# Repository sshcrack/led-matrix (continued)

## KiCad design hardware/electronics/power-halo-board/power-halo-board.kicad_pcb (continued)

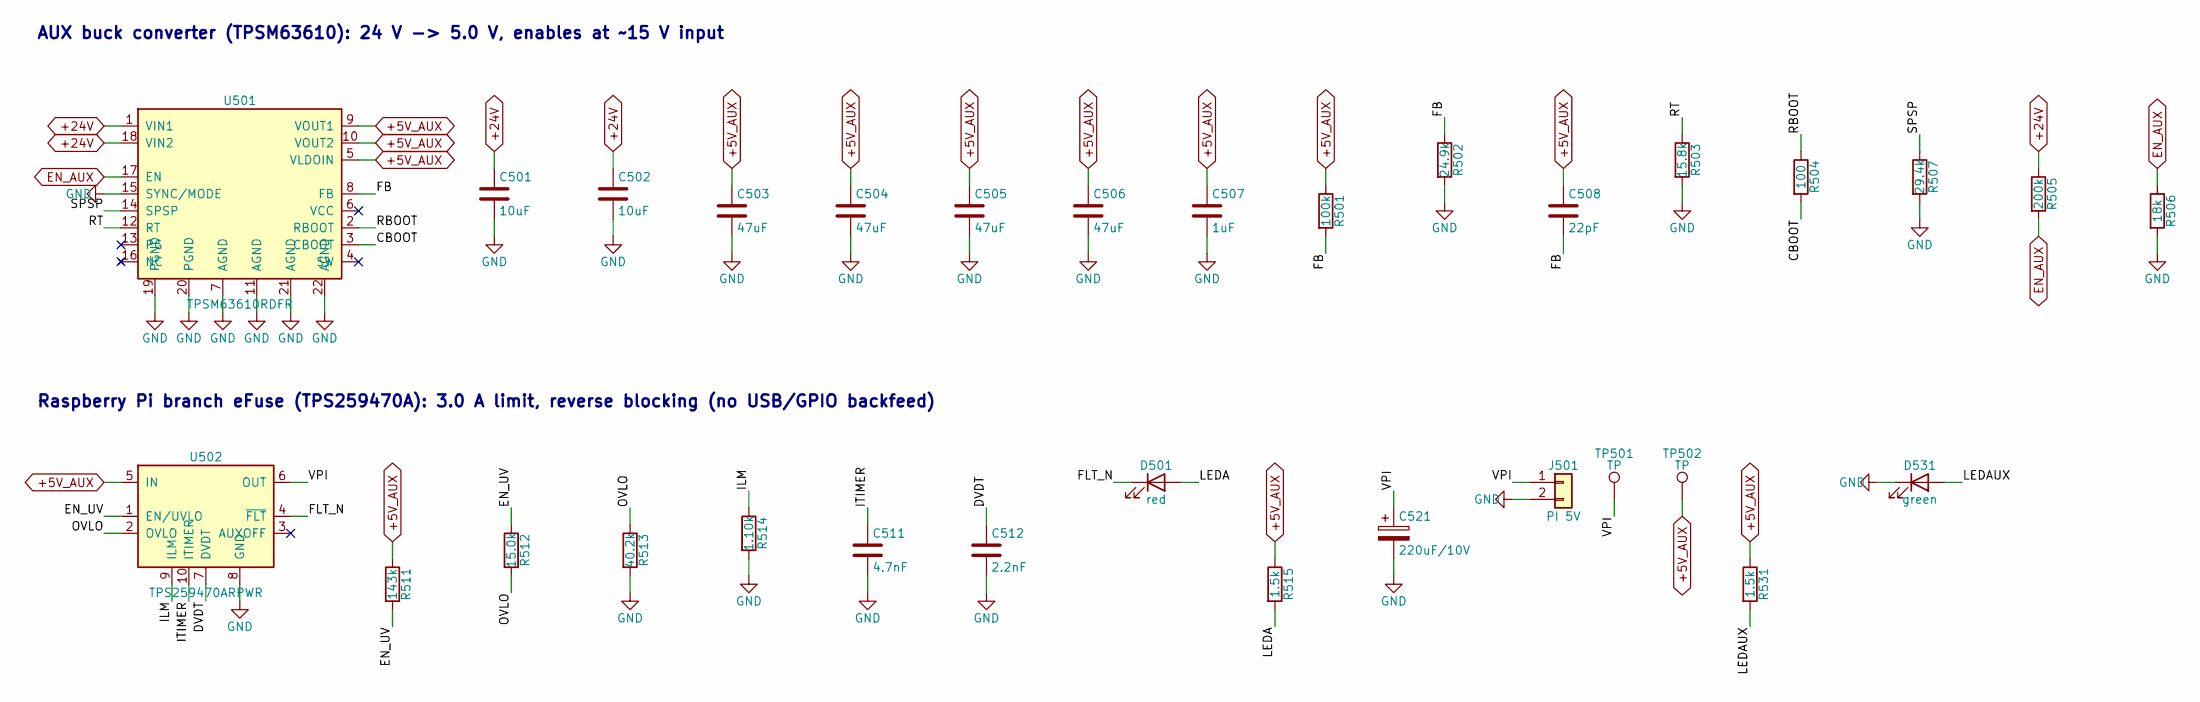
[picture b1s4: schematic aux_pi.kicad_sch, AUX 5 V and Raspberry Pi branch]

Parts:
C501, C502: 10uF; C_1210_3225Metric; Rating 50 V X7R; MPN GRM32ER71H106KA12L
C503, C504, C505, C506: 47uF; C_1210_3225Metric; Rating 10 V X7R; MPN GRM32ER71A476ME15L
C507: 1uF; C_0603_1608Metric; Rating 16 V X7R; MPN GRM188R71C105KA12D
C508: 22pF; C_0603_1608Metric; Rating 50 V C0G; MPN GRM1885C1H220JA01D
C511: 4.7nF; C_0603_1608Metric; Rating 50 V X7R; MPN GRM188R71H472KA01D
C512: 2.2nF; C_0603_1608Metric; Rating 50 V X7R; MPN GRM188R71H222KA01D
C521: 220uF/10V; CP_Elec_8x6.2; Rating 10V; MPN EEE-FK1A221P
D501: red; LED_0603_1608Metric; Rating 20 mA max, run at ~2 mA; MPN APT1608EC
D531: green; LED_0603_1608Metric; Rating 20 mA max, run at ~2 mA; MPN APT1608SGC
J501: PI 5V; JST_VH_S2P-VH_1x02_P3.96mm_Horizontal; Rating 10 A/contact; MPN S2P-VH
R501: 100k; R_0603_1608Metric; Tolerance 1%; Rating 0.1 W, 75 V; MPN RC0603FR-07100KL
R502: 24.9k; R_0603_1608Metric; Tolerance 1%; Rating 0.1 W, 75 V; MPN RC0603FR-0724K9L
R503: 15.8k; R_0603_1608Metric; Tolerance 1%; Rating 0.1 W, 75 V; MPN RC0603FR-0715K8L
R504: 100; R_0603_1608Metric; Tolerance 1%; Rating 0.1 W, 75 V; MPN RC0603FR-07100RL
R505: 200k; R_0603_1608Metric; Tolerance 1%; Rating 0.1 W, 75 V; MPN RC0603FR-07200KL
R506: 18k; R_0603_1608Metric; Tolerance 1%; Rating 0.1 W, 75 V; MPN RC0603FR-0718KL
R507: 29.4k; R_0603_1608Metric; Tolerance 1%; Rating 0.1 W, 75 V; MPN RC0603FR-0729K4L
R511: 143k; R_0603_1608Metric; Tolerance 1%; Rating 0.1 W, 75 V; MPN RC0603FR-07143KL
R512: 15.0k; R_0603_1608Metric; Tolerance 1%; Rating 0.1 W, 75 V; MPN RC0603FR-0715K0L
R513: 40.2k; R_0603_1608Metric; Tolerance 1%; Rating 0.1 W, 75 V; MPN RC0603FR-0740K2L
R514: 1.10k; R_0603_1608Metric; Tolerance 1%; Rating 0.1 W, 75 V; MPN RC0603FR-071K10L
R515, R531: 1.5k; R_0603_1608Metric; Tolerance 1%; Rating 0.1 W, 75 V; MPN RC0603FR-071K5L
TP501, TP502: TP; TestPoint_Pad_D1.5mm
U501: TPSM63610RDFR; TI_RDF0022A_B3QFN-22_6.5x7.5mm; Rating VIN 3-36 V (42 V transient), 8 A; used 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; MPN TPSM63610RDFR
U502: TPS259470ARPWR; TI_RPW0010A_VQFN-HR-10_2x2mm; Rating 2.7-23 V (28 V abs), 5.5 A, 28 mOhm; MPN TPS259470ARPWR

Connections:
+5V_AUX: C503.1, C504.1, C505.1, C506.1, C507.1, C508.1, R501.1, R511.1, R515.1, R531.1, TP502.1, U501.5 (VLDOIN), U501.9 (VOUT1), U501.10 (VOUT2), U502.5 (IN); also elsewhere on the board
+24V: C501.1, C502.1, R505.1, U501.1 (VIN1), U501.18 (VIN2); also elsewhere on the board
/Aux/CBOOT: R504.2, U501.3 (CBOOT)
/Aux/DVDT: C512.1, U502.7 (DVDT)
/Aux/EN_UV: R511.2, R512.1, U502.1 (EN/UVLO)
/Aux/FB: C508.2, R501.2, R502.1, U501.8 (FB)
/Aux/FLT_N: D501.1 (K), U502.4 (~FLT)
/Aux/ILM: R514.1, U502.9 (ILM)
/Aux/ITIMER: C511.1, U502.10 (ITIMER)
/Aux/LEDA: D501.2 (A), R515.2
/Aux/LEDAUX: D531.2 (A), R531.2
/Aux/OVLO: R512.2, R513.1, U502.2 (OVLO)
/Aux/RBOOT: R504.1, U501.2 (RBOOT)
/Aux/RT: R503.1, U501.12 (RT)
/Aux/SPSP: R507.1, U501.14 (SPSP)
/Aux/VPI: C521.1, J501.1, TP501.1, U502.6 (OUT)
EN_AUX: R505.2, R506.1, U501.17 (EN); also elsewhere on the board
GND: C501.2, C502.2, C503.2, C504.2, C505.2, C506.2, C507.2, C511.2, C512.2, C521.2, D531.1 (K), J501.2, R502.2, R503.2, R506.2, R507.2, R513.2, R514.2, U501.7 (AGND), U501.11 (AGND), U501.15 (SYNC/MODE), U501.19 (PGND), U501.20 (PGND), U501.21 (AGND), U501.22 (AGND), U502.8 (GND); also elsewhere on the board

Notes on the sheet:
AUX buck converter (TPSM63610): 24 V -> 5.0 V, enables at ~15 V input
Raspberry Pi branch eFuse (TPS259470A): 3.0 A limit, reverse blocking (no USB/GPIO backfeed)

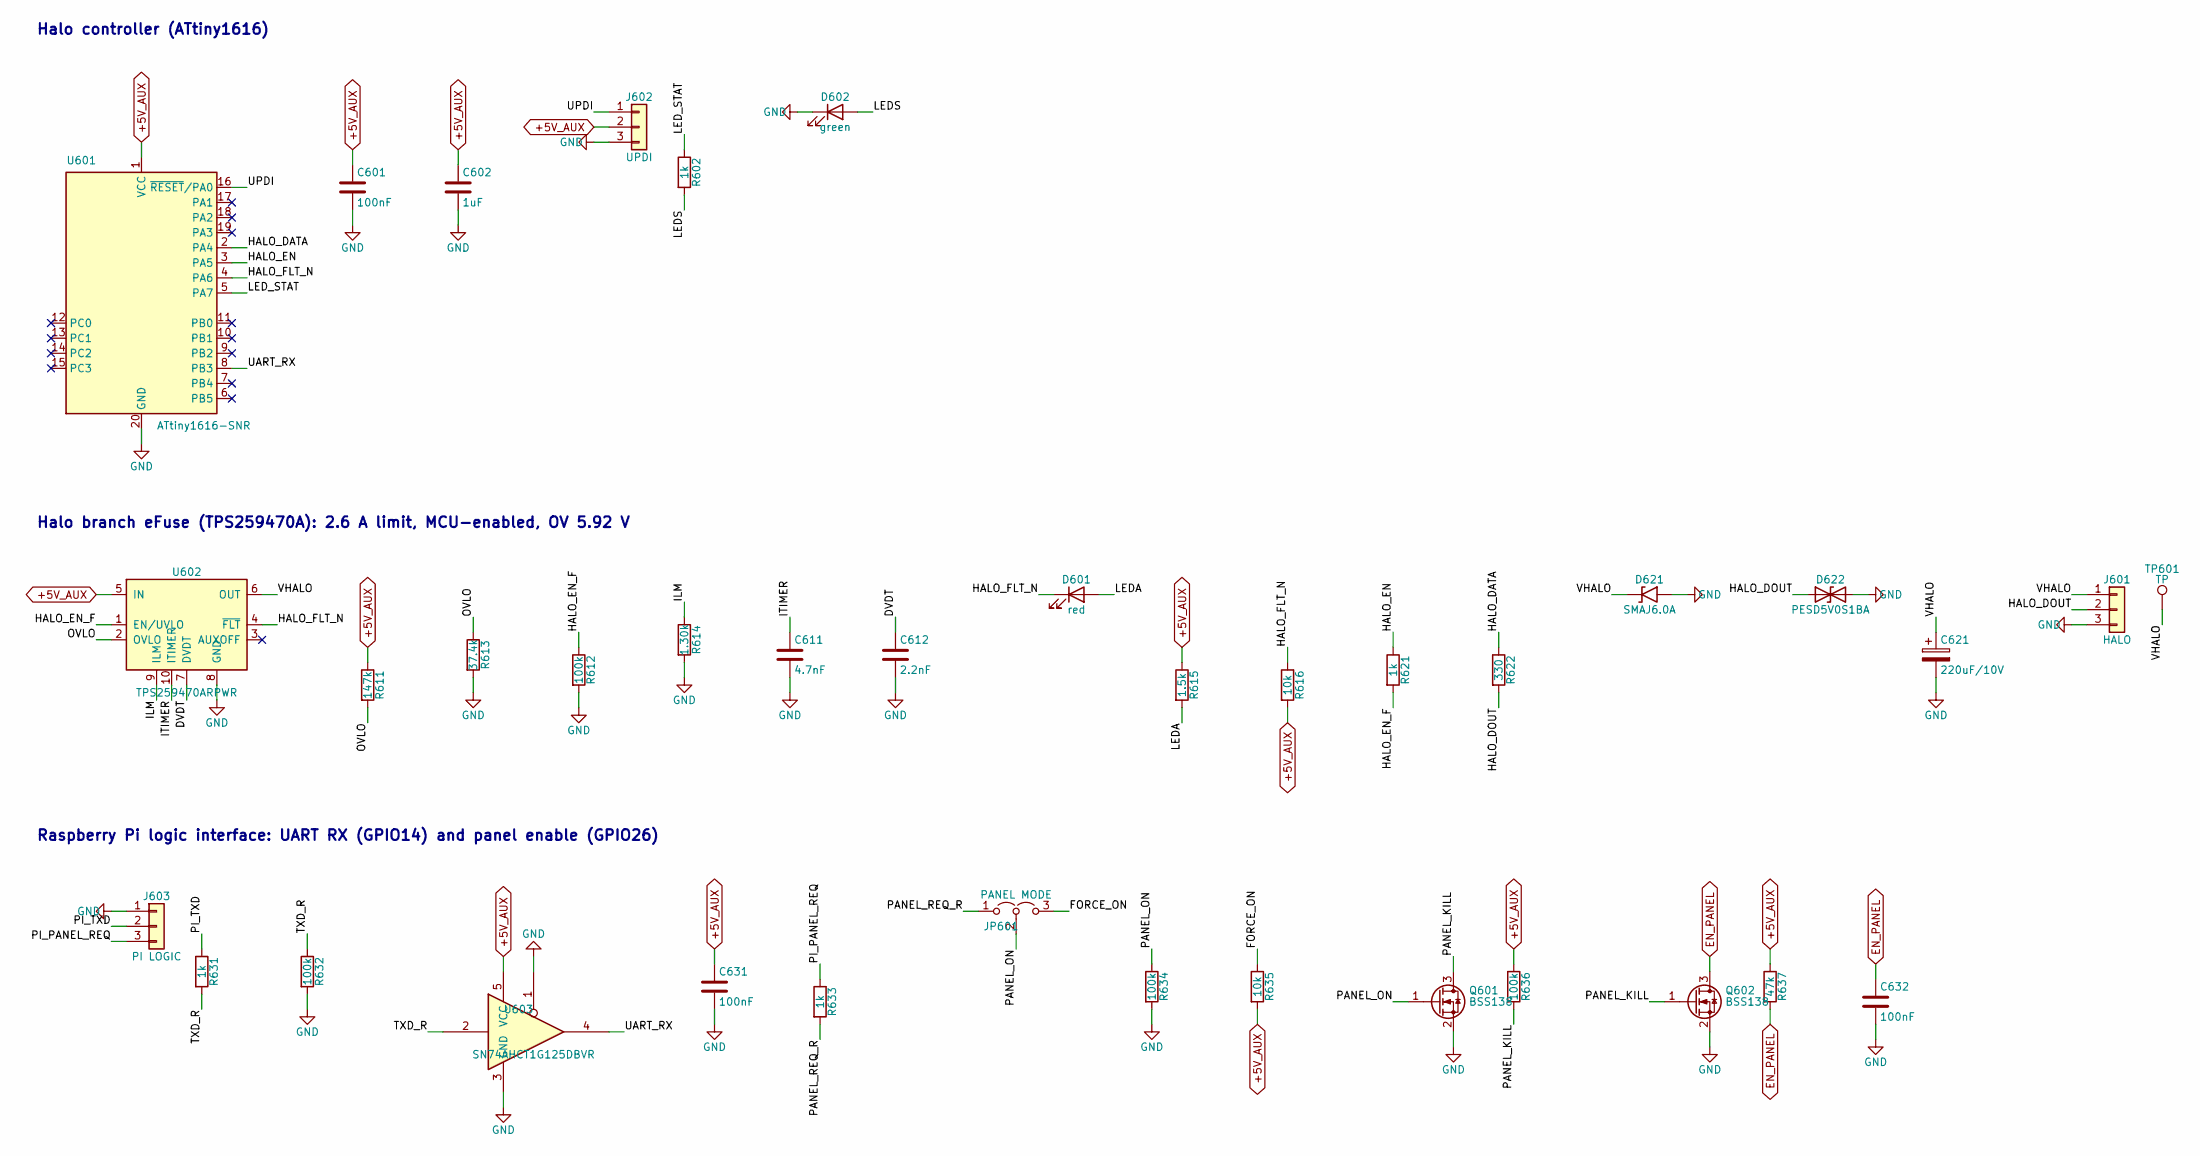
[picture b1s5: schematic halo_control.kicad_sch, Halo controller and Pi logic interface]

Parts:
C601, C631, C632: 100nF; C_0603_1608Metric; Rating 50 V X7R; MPN GRM188R71H104KA93D
C602: 1uF; C_0603_1608Metric; Rating 16 V X7R; MPN GRM188R71C105KA12D
C611: 4.7nF; C_0603_1608Metric; Rating 50 V X7R; MPN GRM188R71H472KA01D
C612: 2.2nF; C_0603_1608Metric; Rating 50 V X7R; MPN GRM188R71H222KA01D
C621: 220uF/10V; CP_Elec_8x6.2; Rating 10V; MPN EEE-FK1A221P
D601: red; LED_0603_1608Metric; Rating 20 mA max, run at ~2 mA; MPN APT1608EC
D602: green; LED_0603_1608Metric; Rating 20 mA max, run at ~2 mA; MPN APT1608SGC
D621: SMAJ6.0A; D_SMA; Rating VRWM 6.0 V, 400 W; MPN SMAJ6.0A
D622: PESD5V0S1BA; D_SOD-323; Rating VRWM 5 V; MPN PESD5V0S1BA
J601: HALO; JST_VH_S3P-VH_1x03_P3.96mm_Horizontal; Rating 10 A/contact; MPN S3P-VH
J602: UPDI; PinHeader_1x03_P2.54mm_Vertical; MPN 61300311121
J603: PI LOGIC; JST_XH_S3B-XH-A_1x03_P2.50mm_Horizontal; Rating 3 A/contact; MPN S3B-XH-A
JP601: PANEL MODE; PinHeader_1x03_P2.54mm_Vertical; MPN 61300311121
Q601: BSS138; SOT-23; Rating 50 V, 0.22 A, Vgs(th) <= 1.5 V; MPN BSS138
Q602: BSS138; SOT-23; Rating 50 V, 0.22 A; MPN BSS138
R602, R621, R631, R633: 1k; R_0603_1608Metric; Tolerance 1%; Rating 0.1 W, 75 V; MPN RC0603FR-071KL
R611: 147k; R_0603_1608Metric; Tolerance 1%; Rating 0.1 W, 75 V; MPN RC0603FR-07147KL
R612, R632, R634, R636: 100k; R_0603_1608Metric; Tolerance 1%; Rating 0.1 W, 75 V; MPN RC0603FR-07100KL
R613: 37.4k; R_0603_1608Metric; Tolerance 1%; Rating 0.1 W, 75 V; MPN RC0603FR-0737K4L
R614: 1.30k; R_0603_1608Metric; Tolerance 1%; Rating 0.1 W, 75 V; MPN RC0603FR-071K30L
R615: 1.5k; R_0603_1608Metric; Tolerance 1%; Rating 0.1 W, 75 V; MPN RC0603FR-071K5L
R616, R635: 10k; R_0603_1608Metric; Tolerance 1%; Rating 0.1 W, 75 V; MPN RC0603FR-0710KL
R622: 330; R_0603_1608Metric; Tolerance 1%; Rating 0.1 W, 75 V; MPN RC0603FR-07330RL
R637: 47k; R_0603_1608Metric; Tolerance 1%; Rating 0.1 W, 75 V; MPN RC0603FR-0747KL
TP601: TP; TestPoint_Pad_D1.5mm
U601: ATtiny1616-SNR; SOIC-20W_7.5x12.8mm_P1.27mm; Rating 1.8-5.5 V, 20 MHz at 4.5-5.5 V; MPN ATtiny1616-SNR
U602: TPS259470ARPWR; TI_RPW0010A_VQFN-HR-10_2x2mm; Rating 2.7-23 V (28 V abs), 5.5 A, 28 mOhm; MPN TPS259470ARPWR
U603: SN74AHCT1G125DBVR; SOT-23-5; Rating 4.5-5.5 V; MPN SN74AHCT1G125DBVR

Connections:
+5V_AUX: C601.1, C602.1, C631.1, J602.2, R611.1, R615.1, R616.2, R635.2, R636.1, R637.1, U601.1 (VCC), U602.5 (IN), U603.5 (VCC); also elsewhere on the board
/Halo/DVDT: C612.1, U602.7 (DVDT)
/Halo/FORCE_ON: JP601.3 (B), R635.1
/Halo/HALO_DATA: R622.1, U601.2 (PA4)
/Halo/HALO_DOUT: D622.1 (A1), J601.2, R622.2
/Halo/HALO_EN: R621.1, U601.3 (PA5)
/Halo/HALO_EN_F: R612.1, R621.2, U602.1 (EN/UVLO)
/Halo/HALO_FLT_N: D601.1 (K), R616.1, U601.4 (PA6), U602.4 (~FLT)
/Halo/ILM: R614.1, U602.9 (ILM)
/Halo/ITIMER: C611.1, U602.10 (ITIMER)
/Halo/LEDA: D601.2 (A), R615.2
/Halo/LEDS: D602.2 (A), R602.2
/Halo/LED_STAT: R602.1, U601.5 (PA7)
/Halo/OVLO: R611.2, R613.1, U602.2 (OVLO)
/Halo/PANEL_KILL: Q601.3 (D), Q602.1 (G), R636.2
/Halo/PANEL_ON: JP601.2 (C), Q601.1 (G), R634.1
/Halo/PANEL_REQ_R: JP601.1 (A), R633.2
/Halo/PI_PANEL_REQ: J603.3, R633.1
/Halo/PI_TXD: J603.2, R631.1
/Halo/TXD_R: R631.2, R632.1, U603.2
/Halo/UART_RX: U601.8 (PB3), U603.4
/Halo/UPDI: J602.1, U601.16 (~RESET/PA0)
/Halo/VHALO: C621.1, D621.1 (K), J601.1, TP601.1, U602.6 (OUT)
EN_PANEL: C632.1, Q602.3 (D), R637.2; also elsewhere on the board
GND: C601.2, C602.2, C611.2, C612.2, C621.2, C631.2, C632.2, D602.1 (K), D621.2 (A), D622.2 (A2), J601.3, J602.3, J603.1, Q601.2 (S), Q602.2 (S), R612.2, R613.2, R614.2, R632.2, R634.2, U601.20 (GND), U602.8 (GND), U603.1, U603.3 (GND); also elsewhere on the board

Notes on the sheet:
Halo controller (ATtiny1616)
Halo branch eFuse (TPS259470A): 2.6 A limit, MCU-enabled, OV 5.92 V
Raspberry Pi logic interface: UART RX (GPIO14) and panel enable (GPIO26)

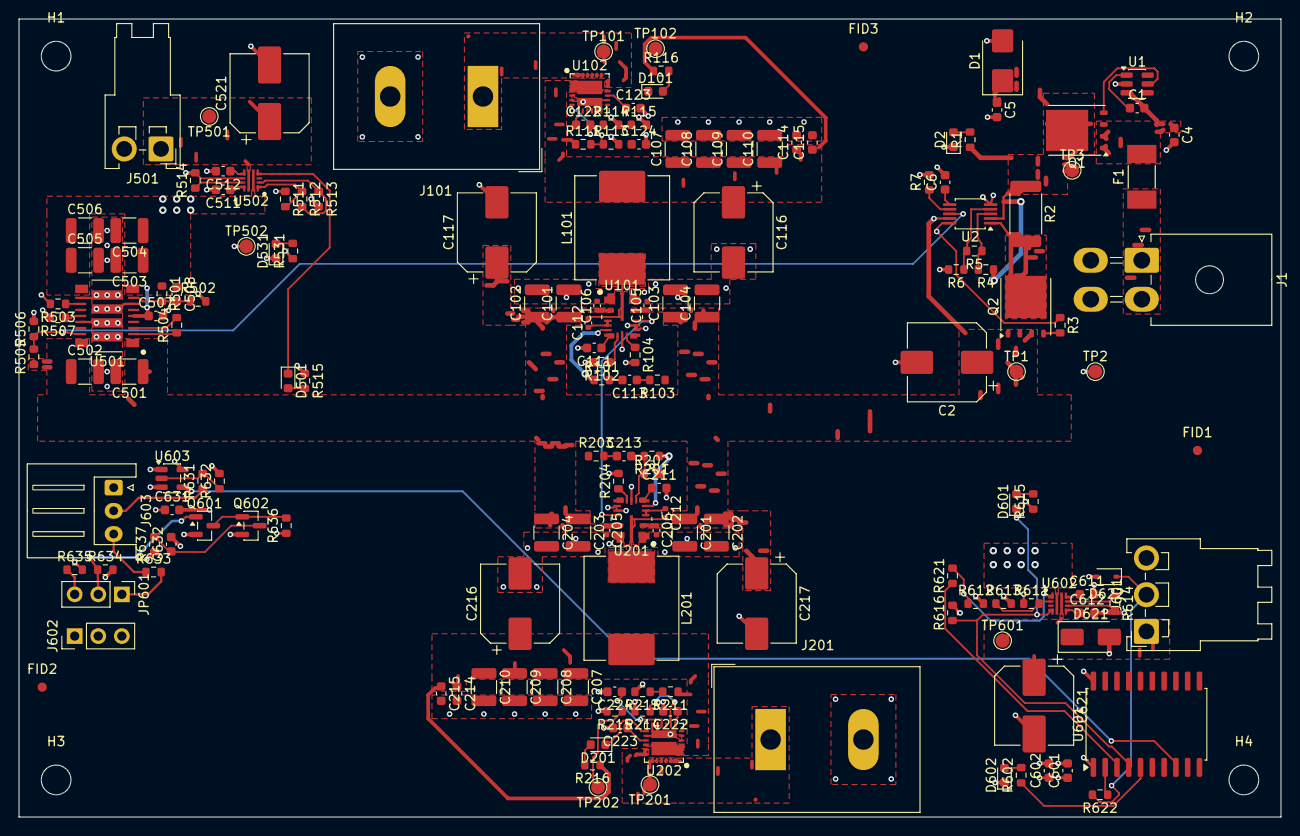
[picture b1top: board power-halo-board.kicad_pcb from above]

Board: 4 copper layers, 136.0 x 86.0 mm, 170 parts (0 on the bottom side), 86 nets.
